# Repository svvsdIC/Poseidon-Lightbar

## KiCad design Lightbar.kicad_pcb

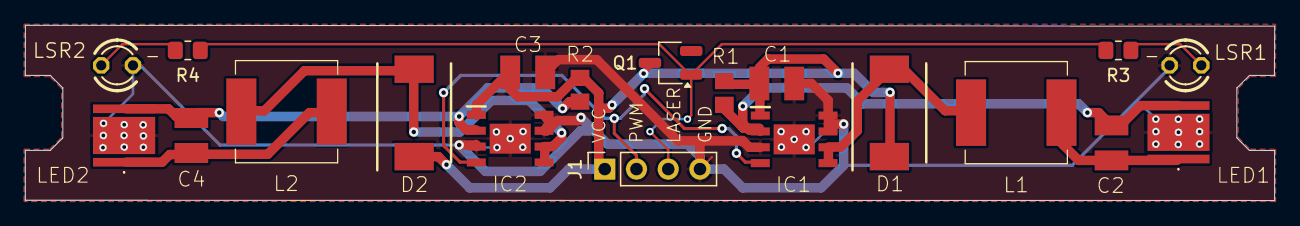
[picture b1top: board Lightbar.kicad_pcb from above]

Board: 2 copper layers, 100.0 x 14.0 mm, 20 parts (0 on the bottom side), 12 nets.

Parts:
C1, C3: 22μF; C1210_334
C2, C4: 10μF; C1210_334
D1, D2: SS34-E3_57T; DIOM7959X262N
IC1, IC2: PAM2863ECR; SOIC127P600X175-9N
J1: Conn_01x04_Pin; PinSocket_1x04_P2.54mm_Vertical
L1, L2: IHLP3232DZER330M11
LED1, LED2: XMLDWT-00-0000-0000U40E2; XMLDWT0000000000U40E2
LSR1, LSR2: TLLG4400; LED3MM_259
Q1: 2N2219; SC-59_Handsoldering
R1, R2: 0.05Ω 1/4W; R0805_334
R3, R4: R_US; R_0805_2012Metric_Pad1.20x1.40mm_HandSolder

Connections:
GND: C1.2, C3.2, IC1.3, IC1.7, IC1.8, IC1.9, IC2.3, IC2.7, IC2.8, IC2.9, J1.4, LED1.3, LED2.3, LSR1.K, LSR2.K
unnamed: C2.1, L1.2, LED1.1
unnamed: C2.2, IC1.2, LED1.2, R1.1
unnamed: C1.1, C3.1, D1.1, D2.1, IC1.1, IC2.1, J1.1, Q1.3 (C), R1.2, R2.2
unnamed: D1.2, IC1.5, IC1.6, L1.1
unnamed: D2.2, IC2.5, IC2.6, L2.1
unnamed: C4.1, L2.2, LED2.1
unnamed: C4.2, IC2.2, LED2.2, R2.1
unnamed: LSR1.A, R3.2
unnamed: LSR2.A, R4.2
unnamed: J1.3, Q1.1 (E), R3.1, R4.1
PWM1: IC1.4, IC2.4, J1.2

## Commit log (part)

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2023-09-28 Create Lightbar Schematic
    The schematic created from the previous two meetings, should be ready to prototype.
2023-10-08 Create Fusion 360 Projects
    Designed Fusion 360 boards from EAGLE schematic. Two versions are included, one with a narrow PCB and another with a square PCB.
2023-10-11 Create Schematic Image
    Quick schematic screenshot for prototypes without needing Fusion 360.
2023-10-25 Create Polygons and Reworks
    After talking with mechanical, it seems like the long PCB would be best. I created polygon layers, which don't carry any power, but could be ground in the future. Added a few other adjustments too. I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
2023-11-06 Create Dual Circuit Board
    Finished a new PCB with two on circuits with one board and connection. Even narrower than previous long board, and was made with the requirements to be 9 cm long or less. Also fixes the trace width a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
2023-11-30 Changed File Organization and Names
2023-12-03 Write PWM and Laser Code
2024-02-26 Added notches and screw holes
2024-02-28 Adjust screw hole size
2024-09-04 Removed Holes
2025-03-05 Sensor Board Update
    I also forgot what I updated here :((
2025-03-06 updated lightbar
    added resistors and transistor
2025-03-12 reworked laser system
2025-03-13 Create Final Gerber Finals
